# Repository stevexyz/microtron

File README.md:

This is a fork of gigatron that is trying to minimize even more the number of components required.

Original project by Marcel van Kervinck and Walter Belgers can be found at https://gigatron.io

Discussion about microtron can be found at https://forum.gigatron.io/viewtopic.php?t=255

Schematic files are edited with KiCAD 6.

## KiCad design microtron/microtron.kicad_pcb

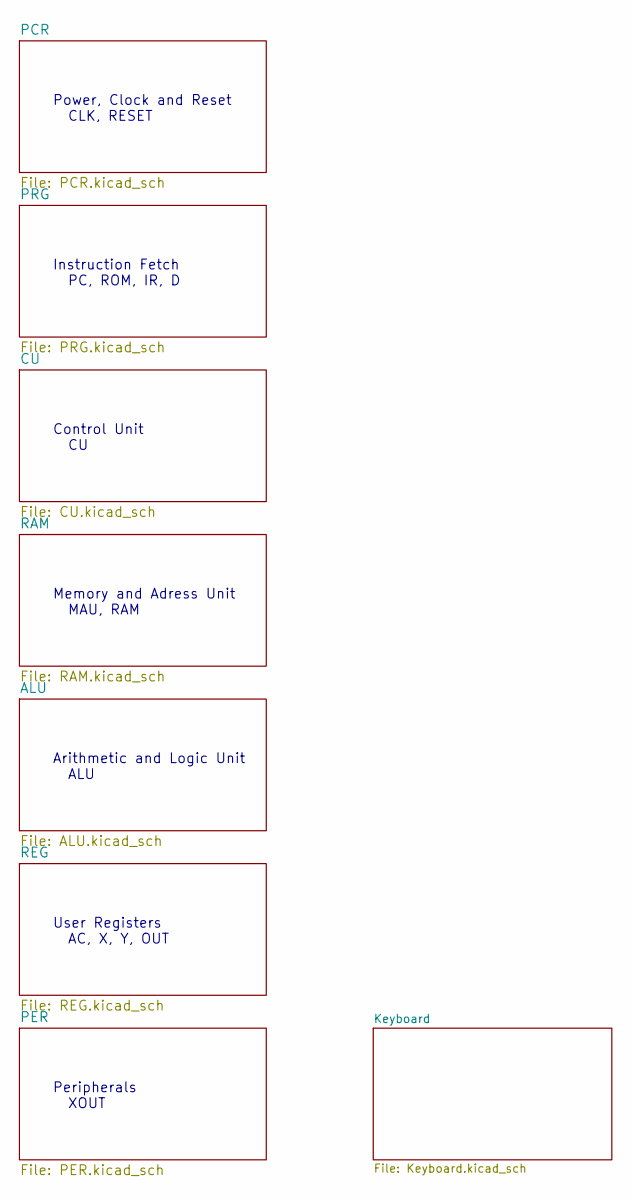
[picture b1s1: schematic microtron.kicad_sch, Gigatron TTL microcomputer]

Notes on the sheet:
Control Unit CU
Instruction Fetch PC, ROM, IR, D
Arithmetic and Logic Unit ALU
Memory and Adress Unit MAU, RAM
User Registers AC, X, Y, OUT
Peripherals XOUT
Power, Clock and Reset CLK, RESET

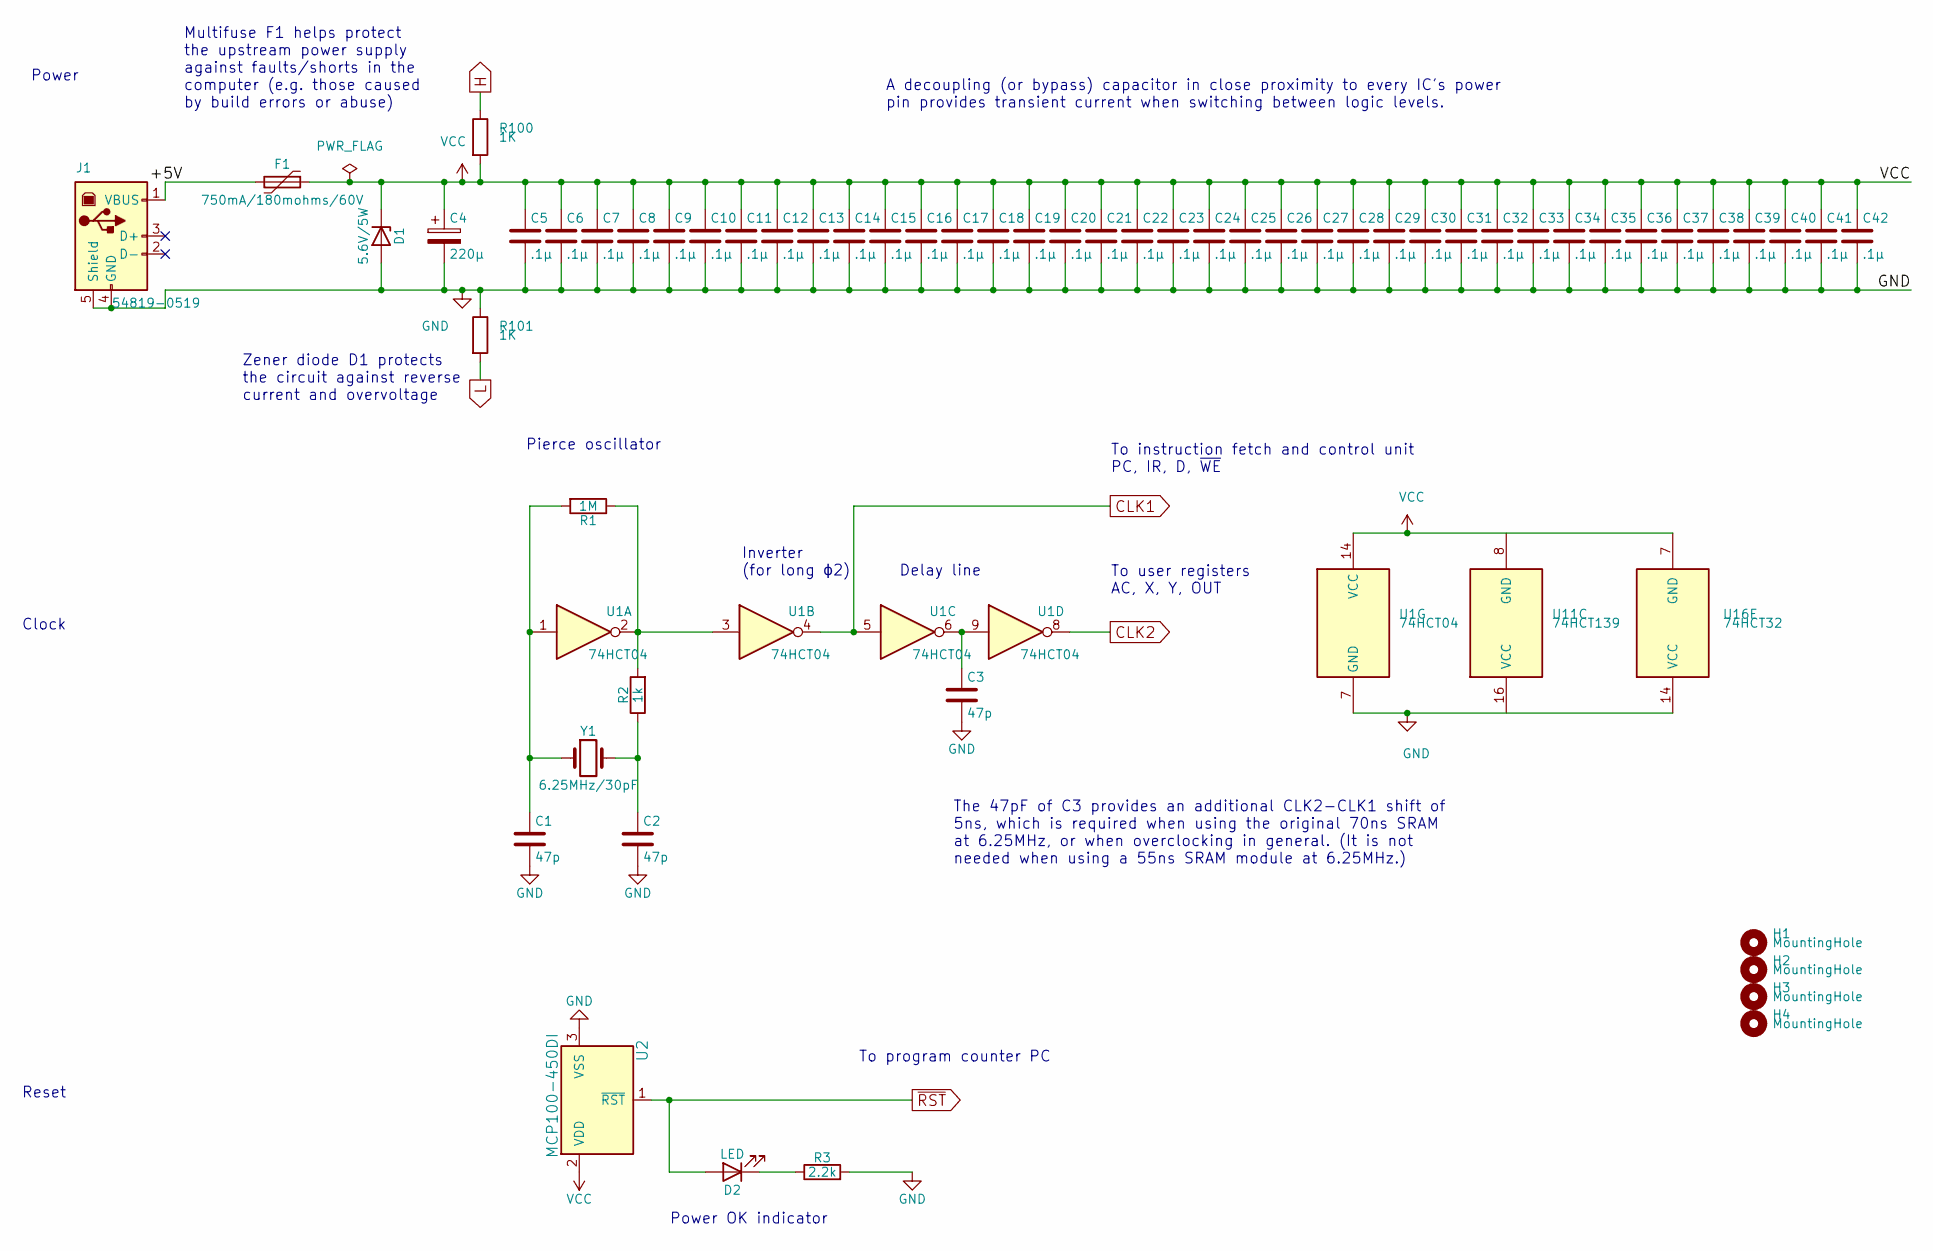
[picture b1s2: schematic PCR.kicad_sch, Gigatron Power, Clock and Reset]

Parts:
C1, C2, C3: 47p; C_Disc_D3.0mm_W2.0mm_P2.50mm
C4: 220µ; CP_Radial_D8.0mm_P3.50mm
C5, C6, C7, C8, C9, C10, C11, C12, C13, C14, C15, C16, C17, C18, C19, C20, C21, C22, C23, C24, C25, C26, C27, C28, C29, C30, C31, C32, C33, C34, C35, C36, C37, C38, C39, C40, C41, C42: .1µ; C_Disc_D4.3mm_W1.9mm_P5.00mm
D1: 5.6V/5W; D_DO-15_P12.70mm_Horizontal
D2: LED; LED_D3.0mm
F1: 750mA/180mohms/60V; Fuse_Littelfuse_395Series
H1, H2, H3, H4: MountingHole; MountingHole_2.7mm_M2.5
J1: 54819-0519; USB_Micro-B_Wuerth_629105150521
R1: 1M; R_Axial_DIN0207_L6.3mm_D2.5mm_P10.16mm_Horizontal
R2: 1k; R_Axial_DIN0207_L6.3mm_D2.5mm_P10.16mm_Horizontal
R3: 2.2k; R_Axial_DIN0207_L6.3mm_D2.5mm_P10.16mm_Horizontal
R100, R101: 1K; R_Axial_DIN0204_L3.6mm_D1.6mm_P1.90mm_Vertical
U1: 74HCT04; DIP-14_W7.62mm
U2: MCP100-450DI; TO-92L_Inline_Wide
U11: 74HCT139; DIP-16_W7.62mm
U16: 74HCT32; DIP-14_W7.62mm
Y1: 6.25MHz/30pF; Crystal_HC49-U_Vertical

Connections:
/PCR/+5V: F1.2, J1.1 (VBUS)
CLK1: U1.4, U1.5; also elsewhere on the board
CLK2: U1.8; also elsewhere on the board
GND: C1.2, C2.2, C3.2, C4.2, C5.2, C6.2, C7.2, C8.2, C9.2, C10.2, C11.2, C12.2, C13.2, C14.2, C15.2, C16.2, C17.2, C18.2, C19.2, C20.2, C21.2, C22.2, C23.2, C24.2, C25.2, C26.2, C27.2, C28.2, C29.2, C30.2, C31.2, C32.2, C33.2, C34.2, C35.2, C36.2, C37.2, C38.2, C39.2, C40.2, C41.2, C42.2, D1.2 (A), J1.4 (GND), J1.5 (Shield), R3.2, R101.1, U1.7 (GND), U2.3 (VSS), U16.14 (VCC); also elsewhere on the board
H: R100.1; also elsewhere on the board
L: R101.2; also elsewhere on the board
unnamed: C1.1, R1.2, U1.1, Y1.1
unnamed: C2.1, R2.1, Y1.2
unnamed: C3.1, U1.6, U1.9
unnamed: D2.1 (K), R3.1
unnamed: R1.1, R2.2, U1.2
VCC: C4.1, C5.1, C6.1, C7.1, C8.1, C9.1, C10.1, C11.1, C12.1, C13.1, C14.1, C15.1, C16.1, C17.1, C18.1, C19.1, C20.1, C21.1, C22.1, C23.1, C24.1, C25.1, C26.1, C27.1, C28.1, C29.1, C30.1, C31.1, C32.1, C33.1, C34.1, C35.1, C36.1, C37.1, C38.1, C39.1, C40.1, C41.1, C42.1, D1.1 (K), F1.1, R100.2, U1.14 (VCC), U2.2 (VDD), U16.7 (GND); also elsewhere on the board
~RST: D2.2 (A), U2.1 (~RST); also elsewhere on the board

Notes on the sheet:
To user registers AC, X, Y, OUT
Zener diode D1 protects the circuit against reverse current and overvoltage
Clock
The 47pF of C3 provides an additional CLK2-CLK1 shift of 5ns, which is required when using the original 70ns SRAM at 6.25MHz, or when overclocking in general. (It is not needed when using a 55ns SRAM module at 6.25MHz.)
Multifuse F1 helps protect the upstream power supply against faults/shorts in the computer (e.g. those caused by build errors or abuse)
To instruction fetch and control unit PC, IR, D, ~{WE}
A decoupling (or bypass) capacitor in close proximity to every IC's power pin provides transient current when switching between logic levels.
Power OK indicator
Power
Inverter (for long ɸ2)
Pierce oscillator
Reset
Delay line
To program counter PC

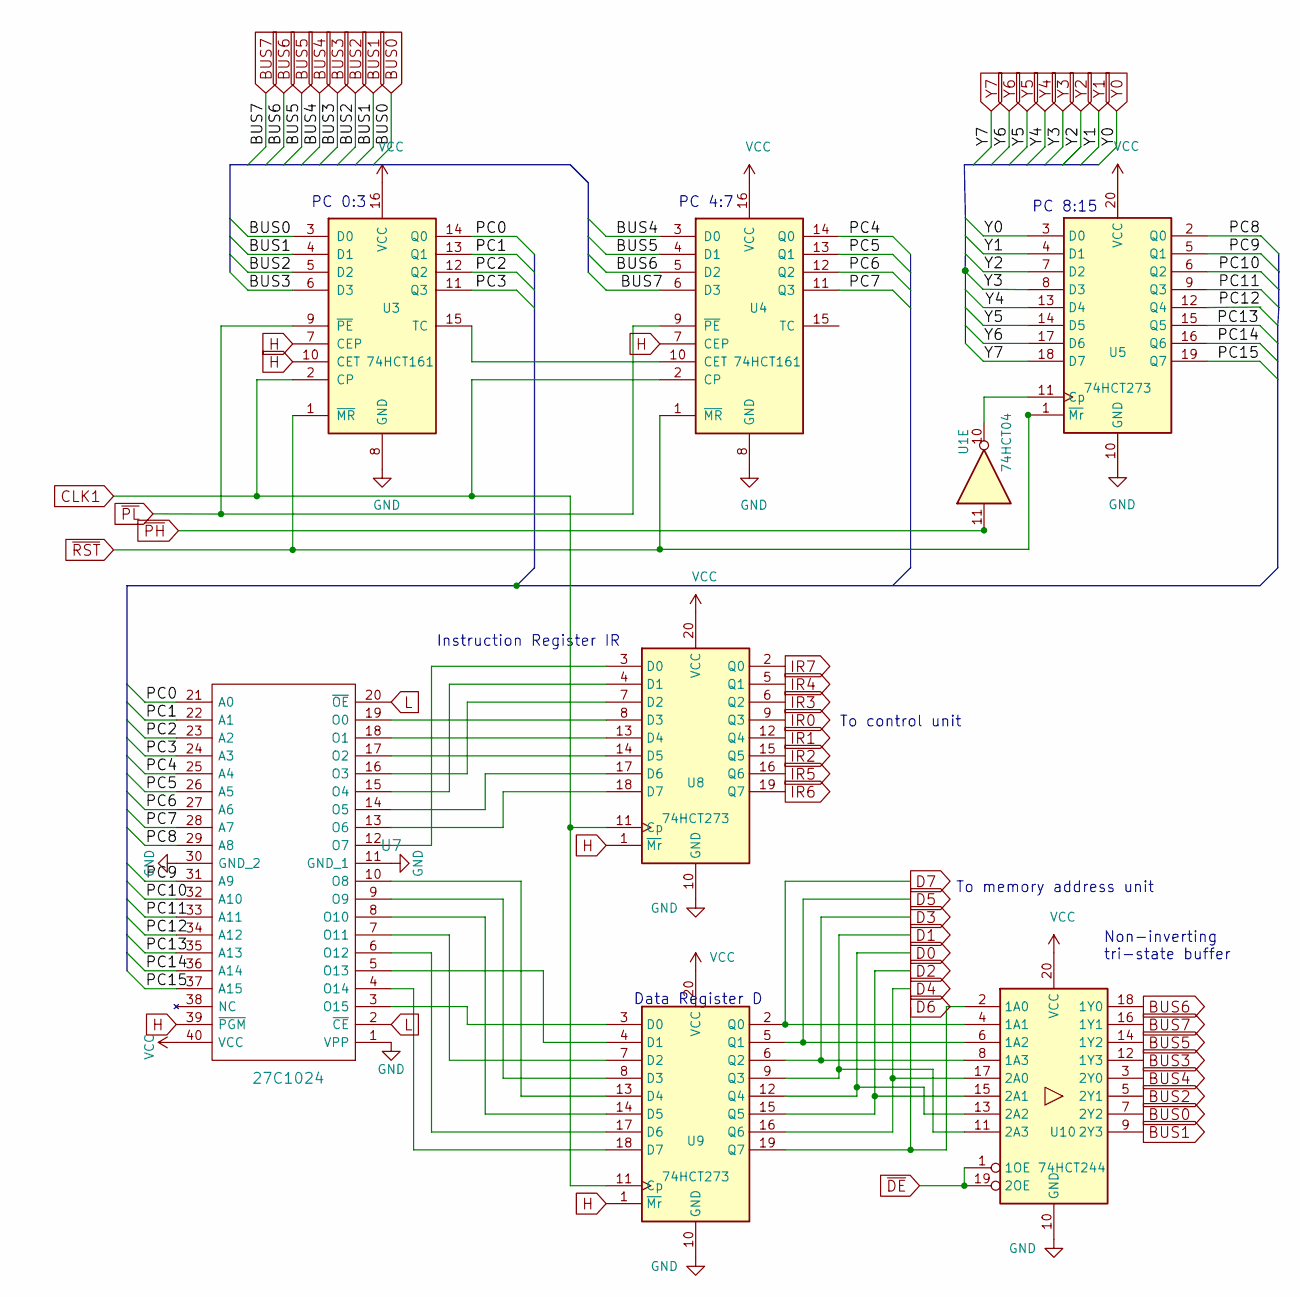
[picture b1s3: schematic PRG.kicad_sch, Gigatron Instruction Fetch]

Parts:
U1: 74HCT04; DIP-14_W7.62mm
U3, U4: 74HCT161; DIP-16_W7.62mm
U5, U8, U9: 74HCT273; DIP-20_W7.62mm
U7: 27C1024; DIP-40_W15.24mm
U10: 74HCT244; DIP-20_W7.62mm

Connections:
/PRG/PC0: U3.14 (Q0), U7.21 (A0)
/PRG/PC1: U3.13 (Q1), U7.22 (A1)
/PRG/PC2: U3.12 (Q2), U7.23 (A2)
/PRG/PC3: U3.11 (Q3), U7.24 (A3)
/PRG/PC4: U4.14 (Q0), U7.25 (A4)
/PRG/PC5: U4.13 (Q1), U7.26 (A5)
/PRG/PC6: U4.12 (Q2), U7.27 (A6)
/PRG/PC7: U4.11 (Q3), U7.28 (A7)
/PRG/PC8: U5.2 (Q0), U7.29 (A8)
/PRG/PC9: U5.5 (Q1), U7.31 (A9)
/PRG/PC10: U5.6 (Q2), U7.32 (A10)
/PRG/PC11: U5.9 (Q3), U7.33 (A11)
/PRG/PC12: U5.12 (Q4), U7.34 (A12)
/PRG/PC13: U5.15 (Q5), U7.35 (A13)
/PRG/PC14: U5.16 (Q6), U7.36 (A14)
/PRG/PC15: U5.19 (Q7), U7.37 (A15)
BUS0: U3.3 (D0), U10.7 (2Y2); also elsewhere on the board
BUS1: U3.4 (D1), U10.9 (2Y3); also elsewhere on the board
BUS2: U3.5 (D2), U10.5 (2Y1); also elsewhere on the board
BUS3: U3.6 (D3), U10.12 (1Y3); also elsewhere on the board
BUS4: U4.3 (D0), U10.3 (2Y0); also elsewhere on the board
BUS5: U4.4 (D1), U10.14 (1Y2); also elsewhere on the board
BUS6: U4.5 (D2), U10.18 (1Y0); also elsewhere on the board
BUS7: U4.6 (D3), U10.16 (1Y1); also elsewhere on the board
CLK1: U3.2 (CP), U4.2 (CP), U8.11 (Cp), U9.11 (Cp); also elsewhere on the board
D0: U9.12 (Q4), U10.13 (2A2); also elsewhere on the board
D1: U9.9 (Q3), U10.11 (2A3); also elsewhere on the board
D2: U9.15 (Q5), U10.15 (2A1); also elsewhere on the board
D3: U9.6 (Q2), U10.8 (1A3); also elsewhere on the board
D4: U9.16 (Q6), U10.17 (2A0); also elsewhere on the board
D5: U9.5 (Q1), U10.6 (1A2); also elsewhere on the board
D6: U9.19 (Q7), U10.2 (1A0); also elsewhere on the board
D7: U9.2 (Q0), U10.4 (1A1); also elsewhere on the board
GND: U3.8 (GND), U4.8 (GND), U5.10 (GND), U7.1 (VPP), U7.11 (GND_1), U7.30 (GND_2), U8.10 (GND), U9.10 (GND), U10.10 (GND); also elsewhere on the board
H: U3.7 (CEP), U3.10 (CET), U4.7 (CEP), U7.39 (~PGM), U8.1 (~Mr), U9.1 (~Mr); also elsewhere on the board
IR0: U8.9 (Q3); also elsewhere on the board
IR1: U8.12 (Q4); also elsewhere on the board
IR2: U8.15 (Q5); also elsewhere on the board
IR3: U8.6 (Q2); also elsewhere on the board
IR4: U8.5 (Q1); also elsewhere on the board
IR5: U8.16 (Q6); also elsewhere on the board
IR6: U8.19 (Q7); also elsewhere on the board
IR7: U8.2 (Q0); also elsewhere on the board
L: U7.2 (~CE), U7.20 (~OE); also elsewhere on the board
unnamed: U1.10, U5.11 (Cp)
unnamed: U3.15 (TC), U4.10 (CET)
unnamed: U7.3 (O15), U9.3 (D0)
unnamed: U7.4 (O14), U9.18 (D7)
unnamed: U7.5 (O13), U9.4 (D1)
unnamed: U7.6 (O12), U9.17 (D6)
unnamed: U7.7 (O11), U9.7 (D2)
unnamed: U7.8 (O10), U9.14 (D5)
unnamed: U7.9 (O9), U9.8 (D3)
unnamed: U7.10 (O8), U9.13 (D4)
unnamed: U7.12 (O7), U8.3 (D0)
unnamed: U7.13 (O6), U8.18 (D7)
unnamed: U7.14 (O5), U8.17 (D6)
unnamed: U7.15 (O4), U8.4 (D1)
unnamed: U7.16 (O3), U8.7 (D2)
unnamed: U7.17 (O2), U8.14 (D5)
unnamed: U7.18 (O1), U8.13 (D4)
unnamed: U7.19 (O0), U8.8 (D3)
VCC: U3.16 (VCC), U4.16 (VCC), U5.20 (VCC), U7.40 (VCC), U8.20 (VCC), U9.20 (VCC), U10.20 (VCC); also elsewhere on the board
Y0: U5.3 (D0); also elsewhere on the board
Y1: U5.4 (D1); also elsewhere on the board
Y2: U5.7 (D2); also elsewhere on the board
Y3: U5.8 (D3); also elsewhere on the board
Y4: U5.13 (D4); also elsewhere on the board
Y5: U5.14 (D5); also elsewhere on the board
Y6: U5.17 (D6); also elsewhere on the board
Y7: U5.18 (D7); also elsewhere on the board
~DE: U10.1 (1OE), U10.19 (2OE); also elsewhere on the board
~PL: U3.9 (~PE), U4.9 (~PE); also elsewhere on the board
~RST: U3.1 (~MR), U4.1 (~MR), U5.1 (~Mr); also elsewhere on the board

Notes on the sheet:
Data Register D
PC 0:3
To control unit
Non-inverting tri-state buffer
Instruction Register IR
PC 8:15
PC 4:7
To memory address unit

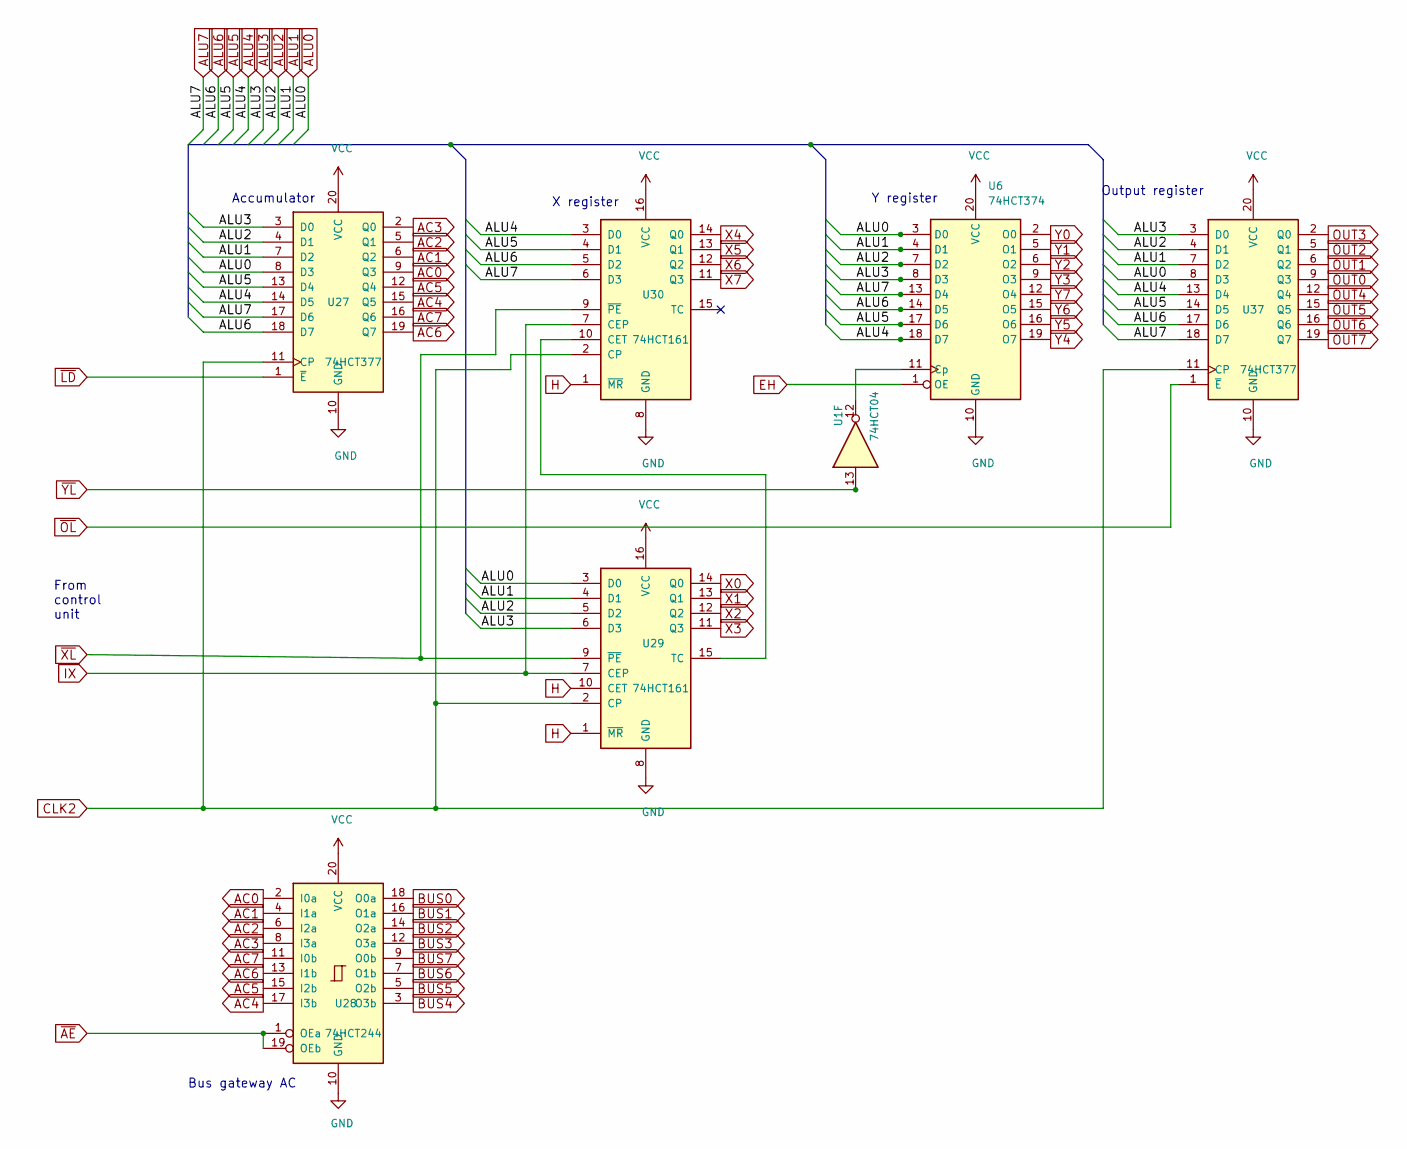
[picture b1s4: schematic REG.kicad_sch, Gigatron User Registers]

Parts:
U1: 74HCT04; DIP-14_W7.62mm
U6: 74HCT374; DIP-20_W7.62mm
U27, U37: 74HCT377; DIP-20_W7.62mm
U28: 74HCT244; DIP-20_W7.62mm
U29, U30: 74HCT161; DIP-16_W7.62mm

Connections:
AC0: U27.9 (Q3), U28.2 (I0a); also elsewhere on the board
AC1: U27.6 (Q2), U28.4 (I1a); also elsewhere on the board
AC2: U27.5 (Q1), U28.6 (I2a); also elsewhere on the board
AC3: U27.2 (Q0), U28.8 (I3a); also elsewhere on the board
AC4: U27.15 (Q5), U28.17 (I3b); also elsewhere on the board
AC5: U27.12 (Q4), U28.15 (I2b); also elsewhere on the board
AC6: U27.19 (Q7), U28.13 (I1b); also elsewhere on the board
AC7: U27.16 (Q6), U28.11 (I0b); also elsewhere on the board
ALU0: U27.8 (D3), U29.3 (D0), U37.8 (D3); also elsewhere on the board
ALU1: U27.7 (D2), U29.4 (D1), U37.7 (D2); also elsewhere on the board
ALU2: U27.4 (D1), U29.5 (D2), U37.4 (D1); also elsewhere on the board
ALU3: U27.3 (D0), U29.6 (D3), U37.3 (D0); also elsewhere on the board
ALU4: U27.14 (D5), U30.3 (D0), U37.13 (D4); also elsewhere on the board
ALU5: U27.13 (D4), U30.4 (D1), U37.14 (D5); also elsewhere on the board
ALU6: U27.18 (D7), U30.5 (D2), U37.17 (D6); also elsewhere on the board
ALU7: U27.17 (D6), U30.6 (D3), U37.18 (D7); also elsewhere on the board
BUS0: U28.18 (O0a); also elsewhere on the board
BUS1: U28.16 (O1a); also elsewhere on the board
BUS2: U28.14 (O2a); also elsewhere on the board
BUS3: U28.12 (O3a); also elsewhere on the board
BUS4: U28.3 (O3b); also elsewhere on the board
BUS5: U28.5 (O2b); also elsewhere on the board
BUS6: U28.7 (O1b); also elsewhere on the board
BUS7: U28.9 (O0b); also elsewhere on the board
CLK2: U27.11 (CP), U29.2 (CP), U30.2 (CP), U37.11 (CP); also elsewhere on the board
EH: U6.1 (OE); also elsewhere on the board
GND: U6.10 (GND), U27.10 (GND), U28.10 (GND), U29.8 (GND), U30.8 (GND), U37.10 (GND); also elsewhere on the board
H: U29.1 (~MR), U29.10 (CET), U30.1 (~MR); also elsewhere on the board
IX: U29.7 (CEP), U30.7 (CEP); also elsewhere on the board
unnamed: U1.12, U6.11 (Cp)
unnamed: U29.15 (TC), U30.10 (CET)
OUT0: U37.9 (Q3); also elsewhere on the board
OUT1: U37.6 (Q2); also elsewhere on the board
OUT2: U37.5 (Q1); also elsewhere on the board
OUT3: U37.2 (Q0); also elsewhere on the board
OUT4: U37.12 (Q4); also elsewhere on the board
OUT5: U37.15 (Q5); also elsewhere on the board
OUT6: U37.16 (Q6); also elsewhere on the board
OUT7: U37.19 (Q7); also elsewhere on the board
VCC: U6.20 (VCC), U27.20 (VCC), U28.20 (VCC), U29.16 (VCC), U30.16 (VCC), U37.20 (VCC); also elsewhere on the board
X0: U29.14 (Q0); also elsewhere on the board
X1: U29.13 (Q1); also elsewhere on the board
X2: U29.12 (Q2); also elsewhere on the board
X3: U29.11 (Q3); also elsewhere on the board
X4: U30.14 (Q0); also elsewhere on the board
X5: U30.13 (Q1); also elsewhere on the board
X6: U30.12 (Q2); also elsewhere on the board
X7: U30.11 (Q3); also elsewhere on the board
Y0: U6.2 (O0); also elsewhere on the board
Y1: U6.5 (O1); also elsewhere on the board
Y2: U6.6 (O2); also elsewhere on the board
Y3: U6.9 (O3); also elsewhere on the board
Y4: U6.19 (O7); also elsewhere on the board
Y5: U6.16 (O6); also elsewhere on the board
Y6: U6.15 (O5); also elsewhere on the board
Y7: U6.12 (O4); also elsewhere on the board
~AE: U28.1 (OEa), U28.19 (OEb); also elsewhere on the board
~LD: U27.1 (~E); also elsewhere on the board
~OL: U37.1 (~E); also elsewhere on the board
~XL: U29.9 (~PE), U30.9 (~PE); also elsewhere on the board

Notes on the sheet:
Accumulator
Output register
Bus gateway AC
X register
Y register
From control unit

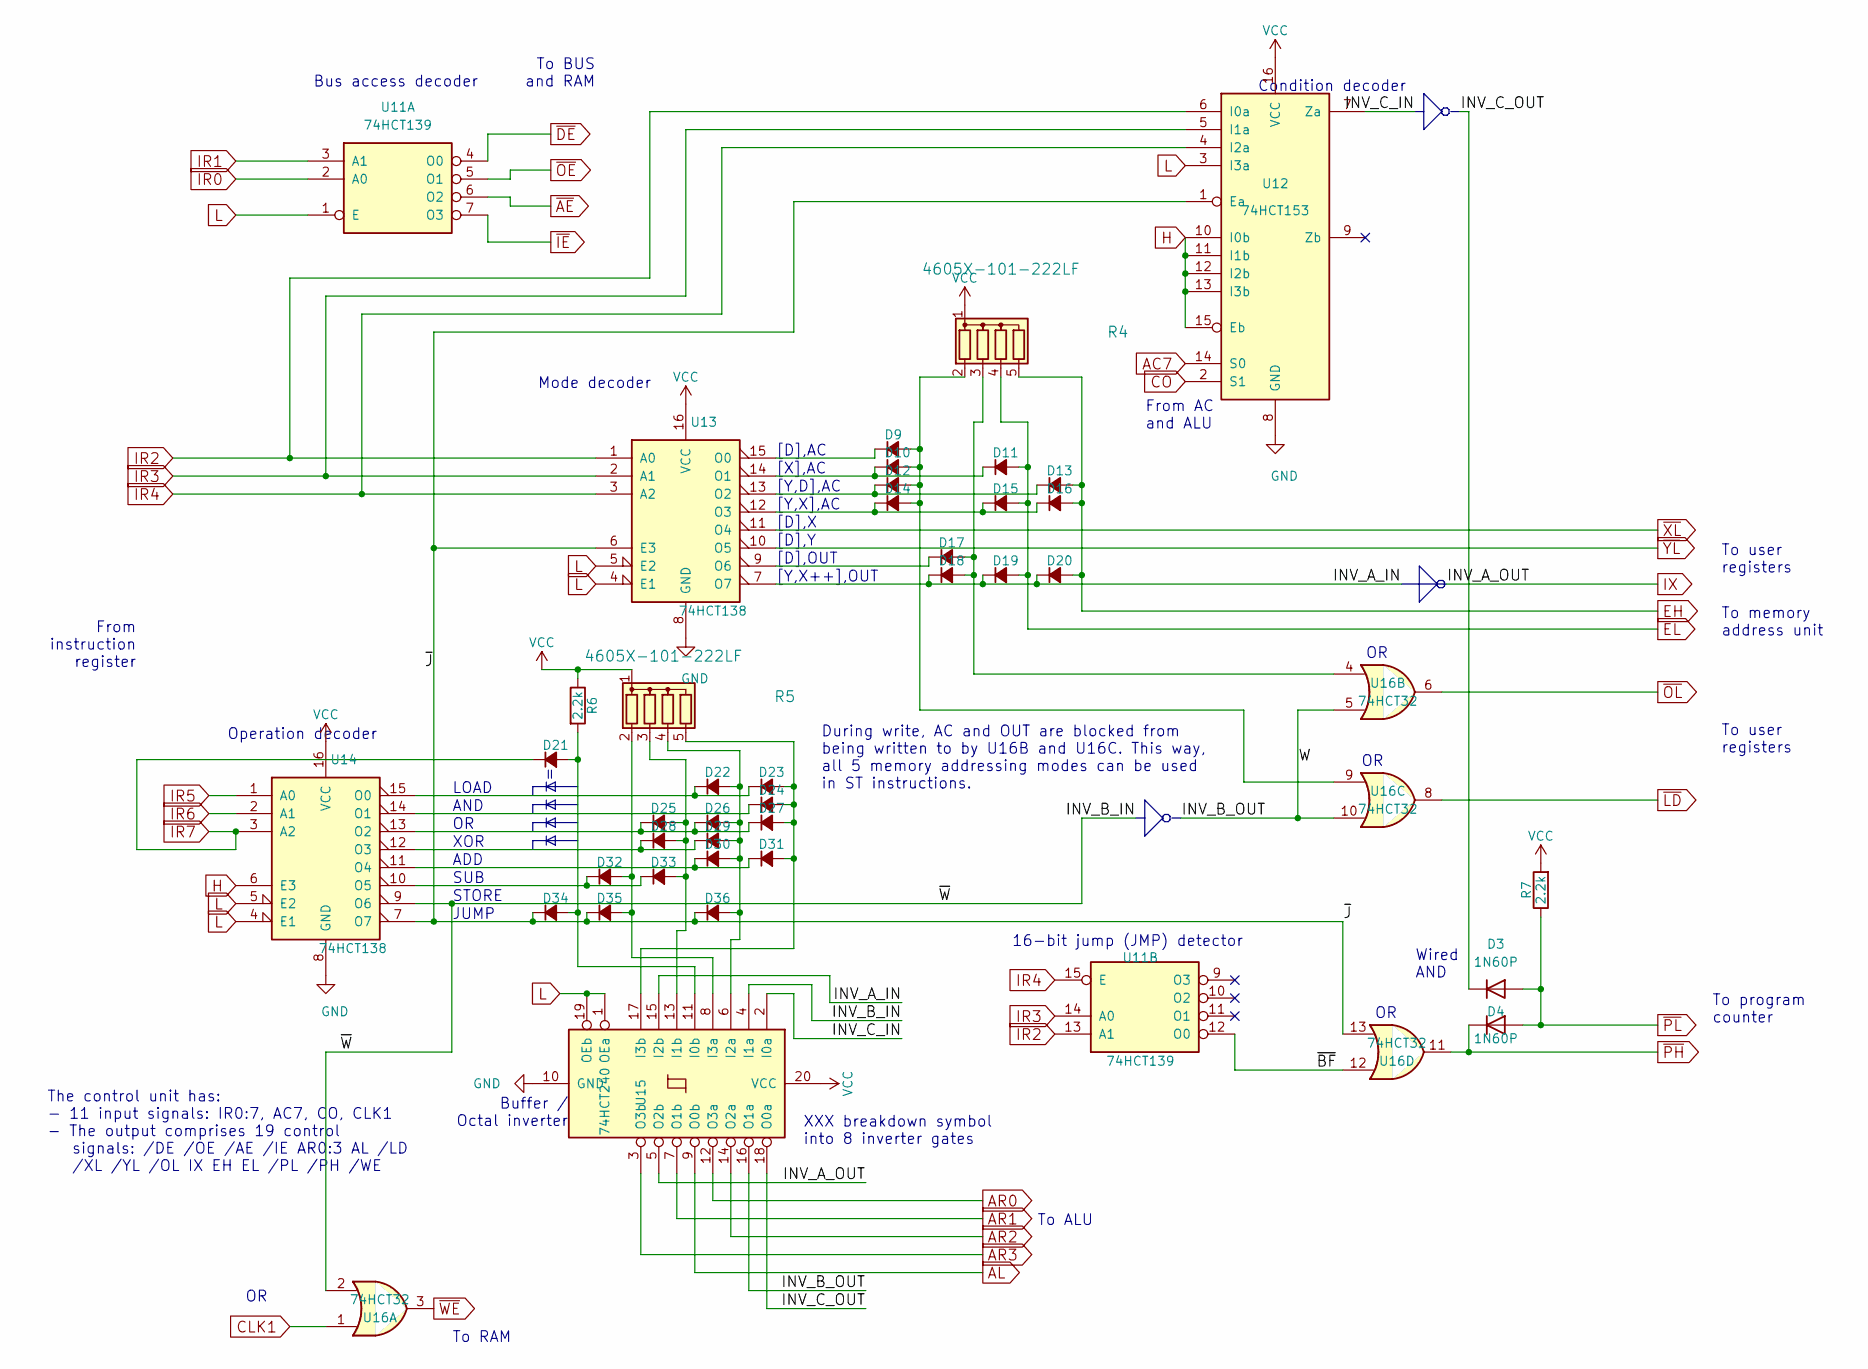
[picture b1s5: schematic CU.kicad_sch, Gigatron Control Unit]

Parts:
D3, D4: 1N60P; D_A-405_P7.62mm_Horizontal
D9, D10, D11, D12, D13, D14, D15, D16, D17, D18, D19, D20, D21, D22, D23, D24, D25, D26, D27, D28, D29, D30, D31, D32, D33, D34, D35, D36: 1N60P; D_A-405_P2.54mm_Vertical_KathodeUp
R4, R5: 4605X-101-222LF; R_Array_SIP5
R6, R7: 2.2k; R_Axial_DIN0207_L6.3mm_D2.5mm_P10.16mm_Horizontal
U11: 74HCT139; DIP-16_W7.62mm
U12: 74HCT153; DIP-16_W7.62mm
U13, U14: 74HCT138; DIP-16_W7.62mm
U15: 74HCT240; DIP-20_W7.62mm
U16: 74HCT32; DIP-14_W7.62mm

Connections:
/CU/INV_A_IN: D18.1 (K), D19.1 (K), D20.1 (K), U13.7 (O7), U15.15 (I2b)
/CU/INV_B_IN: U14.9 (O6), U15.4 (I1a), U16.2
/CU/INV_B_OUT: U15.16 (O1a), U16.5, U16.10
/CU/INV_C_IN: U12.7 (Za), U15.2 (I0a)
/CU/INV_C_OUT: D3.1 (K), U15.18 (O0a)
/CU/~BF: U11.12 (O0), U16.12
/CU/~J: D34.1 (K), D35.1 (K), D36.1 (K), U12.1 (Ea), U13.6 (E3), U14.7 (O7), U16.13
AC7: U12.14 (S0); also elsewhere on the board
AL: U15.9 (O0b); also elsewhere on the board
AR0: U15.12 (O3a); also elsewhere on the board
AR1: U15.7 (O1b); also elsewhere on the board
AR2: U15.14 (O2a); also elsewhere on the board
AR3: U15.3 (O3b); also elsewhere on the board
CLK1: U16.1; also elsewhere on the board
CO: U12.2 (S1); also elsewhere on the board
EH: D13.2 (A), D16.2 (A), D20.2 (A), R4.5 (R4); also elsewhere on the board
EL: D11.2 (A), D15.2 (A), D19.2 (A), R4.4 (R3); also elsewhere on the board
GND: U12.8 (GND), U13.8 (GND), U14.8 (GND), U15.10 (GND); also elsewhere on the board
H: U12.10 (I0b), U12.11 (I1b), U12.12 (I2b), U12.13 (I3b), U12.15 (Eb), U14.6 (E3); also elsewhere on the board
IR0: U11.2 (A0); also elsewhere on the board
IR1: U11.3 (A1); also elsewhere on the board
IR2: U11.13 (A1), U12.6 (I0a), U13.1 (A0); also elsewhere on the board
IR3: U11.14 (A0), U12.5 (I1a), U13.2 (A1); also elsewhere on the board
IR4: U11.15 (E), U12.4 (I2a), U13.3 (A2); also elsewhere on the board
IR5: U14.1 (A0); also elsewhere on the board
IR6: U14.2 (A1); also elsewhere on the board
IR7: D21.1 (K), U14.3 (A2); also elsewhere on the board
IX: U15.5 (O2b); also elsewhere on the board
L: U11.1 (E), U12.3 (I3a), U13.4 (E1), U13.5 (E2), U14.4 (E1), U14.5 (E2), U15.1 (OEa), U15.19 (OEb); also elsewhere on the board
unnamed: D9.1 (K), U13.15 (O0)
unnamed: D10.1 (K), D11.1 (K), U13.14 (O1)
unnamed: D9.2 (A), D10.2 (A), D12.2 (A), D14.2 (A), R4.2 (R1), U16.9
unnamed: D12.1 (K), D13.1 (K), U13.13 (O2)
unnamed: D14.1 (K), D15.1 (K), D16.1 (K), U13.12 (O3)
unnamed: D17.1 (K), U13.9 (O6)
unnamed: D17.2 (A), D18.2 (A), R4.3 (R2), U16.4
unnamed: D21.2 (A), D34.2 (A), R6.2, U15.11 (I0b)
unnamed: D22.1 (K), D23.1 (K), U14.15 (O0)
unnamed: D22.2 (A), D26.2 (A), D29.2 (A), D30.2 (A), D36.2 (A), R5.4 (R3), U15.6 (I2a)
unnamed: D23.2 (A), D24.2 (A), D27.2 (A), D31.2 (A), R5.5 (R4), U15.17 (I3b)
unnamed: D24.1 (K), U14.14 (O1)
unnamed: D25.1 (K), D26.1 (K), D27.1 (K), U14.13 (O2)
unnamed: D25.2 (A), D28.2 (A), D33.2 (A), R5.3 (R2), U15.13 (I1b)
unnamed: D28.1 (K), D29.1 (K), U14.12 (O3)
unnamed: D30.1 (K), D31.1 (K), U14.11 (O4)
unnamed: D32.1 (K), D33.1 (K), U14.10 (O5)
unnamed: D32.2 (A), D35.2 (A), R5.2 (R1), U15.8 (I3a)
VCC: R4.1 (common), R5.1 (common), R6.1, R7.2, U12.16 (VCC), U13.16 (VCC), U14.16 (VCC), U15.20 (VCC); also elsewhere on the board
~AE: U11.6 (O2); also elsewhere on the board
~DE: U11.4 (O0); also elsewhere on the board
~IE: U11.7 (O3); also elsewhere on the board
~LD: U16.8; also elsewhere on the board
~OE: U11.5 (O1); also elsewhere on the board
~OL: U16.6; also elsewhere on the board
~PH: D4.1 (K), U16.11
~PL: D3.2 (A), D4.2 (A), R7.1; also elsewhere on the board
~WE: U16.3; also elsewhere on the board
~XL: U13.11 (O4); also elsewhere on the board
~YL: U13.10 (O5)

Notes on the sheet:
To program counter
JUMP
During write, AC and OUT are blocked from being written to by U16B and U16C. This way, all 5 memory addressing modes can be used in ST instructions.
To user registers
[Y,X],AC
Buffer / Octal inverter
16-bit jump (JMP) detector
From AC and ALU
To RAM
[D],Y
Condition decoder
To memory address unit
Operation decoder
The control unit has: - 11 input signals: IR0:7, AC7, CO, CLK1 - The output comprises 19 control signals: /DE /OE /AE /IE AR0:3 AL /LD /XL /YL /OL IX EH EL /PL /PH /WE
To ALU
XOR
ADD
[D],OUT
STORE
Bus access decoder
[D],X
XXX breakdown symbol into 8 inverter gates
From instruction register
AND
SUB
To BUS and RAM
[Y,D],AC
LOAD
Mode decoder
[D],AC
[Y,X++],OUT
[X],AC
Wired AND

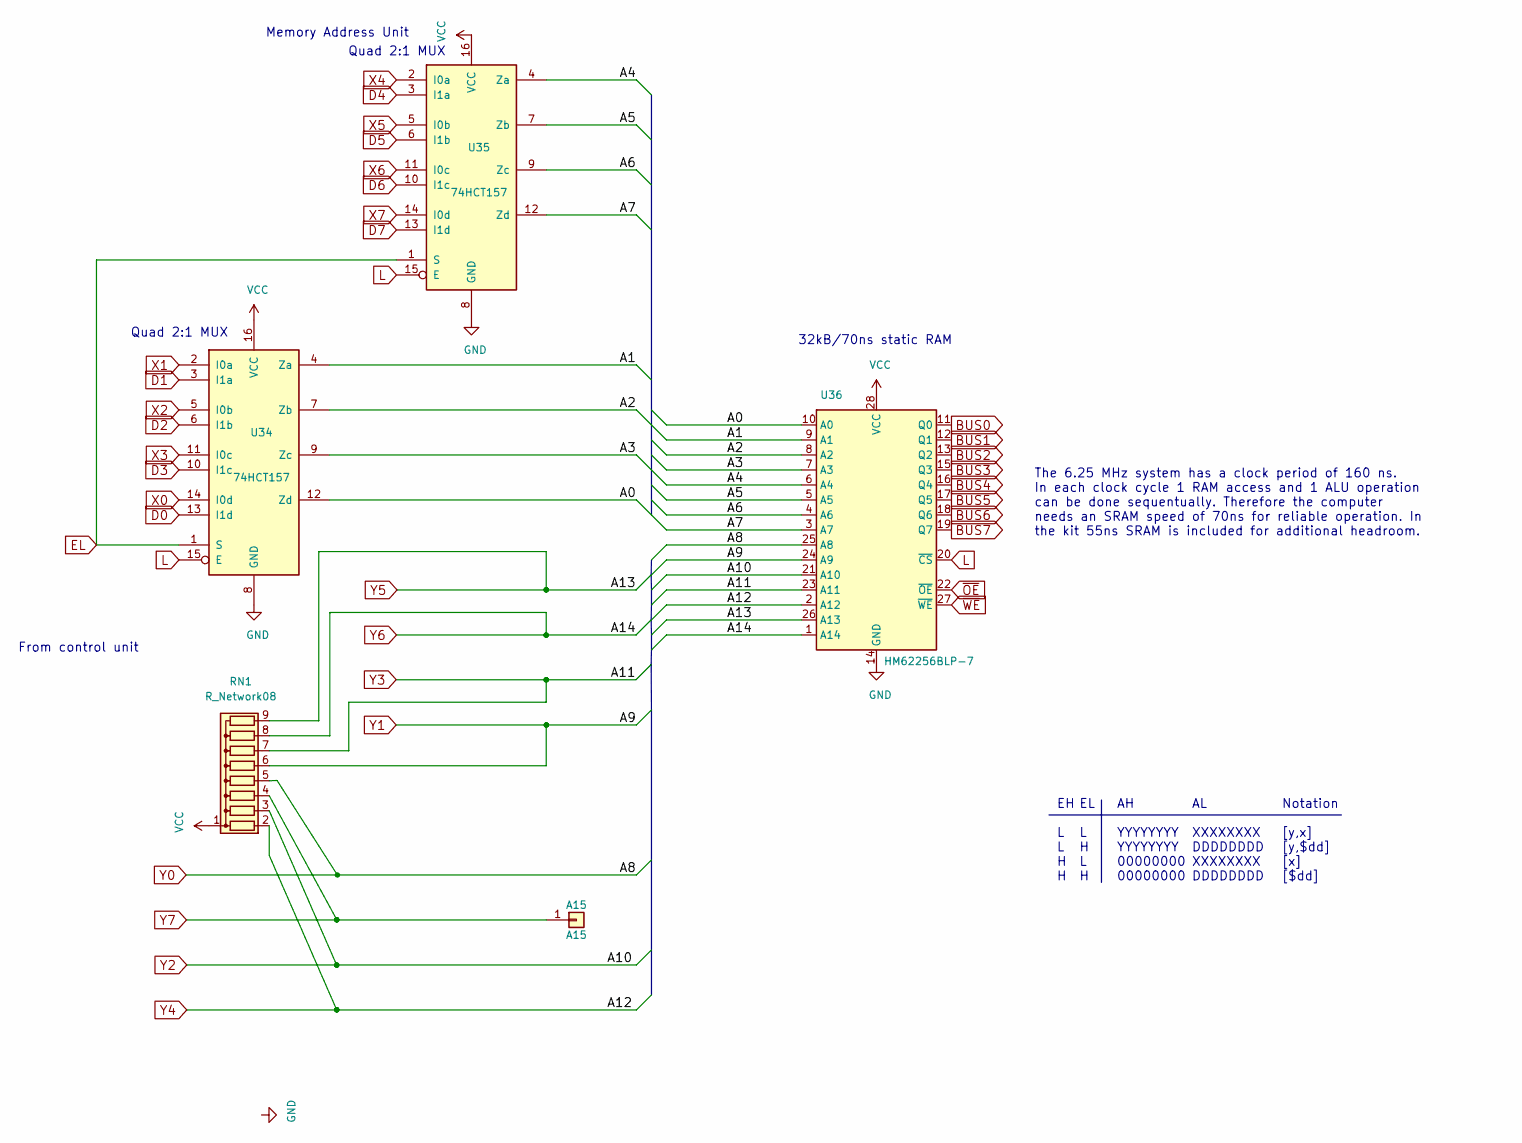
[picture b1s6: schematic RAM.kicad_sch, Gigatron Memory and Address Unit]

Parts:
A15: A15; TestPoint_THTPad_D2.0mm_Drill1.0mm
RN1: R_Network08; R_Array_SIP9
U34, U35: 74HCT157; DIP-16_W7.62mm
U36: HM62256BLP-7; DIP-28_W15.24mm

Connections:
/RAM/A0: U34.12 (Zd), U36.10 (A0)
/RAM/A1: U34.4 (Za), U36.9 (A1)
/RAM/A2: U34.7 (Zb), U36.8 (A2)
/RAM/A3: U34.9 (Zc), U36.7 (A3)
/RAM/A4: U35.4 (Za), U36.6 (A4)
/RAM/A5: U35.7 (Zb), U36.5 (A5)
/RAM/A6: U35.9 (Zc), U36.4 (A6)
/RAM/A7: U35.12 (Zd), U36.3 (A7)
BUS0: U36.11 (Q0); also elsewhere on the board
BUS1: U36.12 (Q1); also elsewhere on the board
BUS2: U36.13 (Q2); also elsewhere on the board
BUS3: U36.15 (Q3); also elsewhere on the board
BUS4: U36.16 (Q4); also elsewhere on the board
BUS5: U36.17 (Q5); also elsewhere on the board
BUS6: U36.18 (Q6); also elsewhere on the board
BUS7: U36.19 (Q7); also elsewhere on the board
D0: U34.13 (I1d); also elsewhere on the board
D1: U34.3 (I1a); also elsewhere on the board
D2: U34.6 (I1b); also elsewhere on the board
D3: U34.10 (I1c); also elsewhere on the board
D4: U35.3 (I1a); also elsewhere on the board
D5: U35.6 (I1b); also elsewhere on the board
D6: U35.10 (I1c); also elsewhere on the board
D7: U35.13 (I1d); also elsewhere on the board
EL: U34.1 (S), U35.1 (S); also elsewhere on the board
GND: U34.8 (GND), U35.8 (GND), U36.14 (GND); also elsewhere on the board
L: U34.15 (E), U35.15 (E), U36.20 (~CS); also elsewhere on the board
VCC: RN1.1 (common), U34.16 (VCC), U35.16 (VCC), U36.28 (VCC); also elsewhere on the board
X0: U34.14 (I0d); also elsewhere on the board
X1: U34.2 (I0a); also elsewhere on the board
X2: U34.5 (I0b); also elsewhere on the board
X3: U34.11 (I0c); also elsewhere on the board
X4: U35.2 (I0a); also elsewhere on the board
X5: U35.5 (I0b); also elsewhere on the board
X6: U35.11 (I0c); also elsewhere on the board
X7: U35.14 (I0d); also elsewhere on the board
Y0: RN1.5 (R4), U36.25 (A8); also elsewhere on the board
Y1: RN1.6 (R5), U36.24 (A9); also elsewhere on the board
Y2: RN1.3 (R2), U36.21 (A10); also elsewhere on the board
Y3: U36.23 (A11); also elsewhere on the board
Y4: RN1.2 (R1), U36.2 (A12); also elsewhere on the board
Y5: RN1.9 (R8), U36.26 (A13); also elsewhere on the board
Y6: RN1.8 (R7), U36.1 (A14); also elsewhere on the board
Y7: A15.1, RN1.4 (R3); also elsewhere on the board
~OE: U36.22 (~OE); also elsewhere on the board
~WE: U36.27 (~WE); also elsewhere on the board

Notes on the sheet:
From control unit
AH YYYYYYYY YYYYYYYY 00000000 00000000
The 6.25 MHz system has a clock period of 160 ns. In each clock cycle 1 RAM access and 1 ALU operation can be done sequentually. Therefore the computer needs an SRAM speed of 70ns for reliable operation. In the kit 55ns SRAM is included for additional headroom.
Quad 2:1 MUX
EH L L H H
AL XXXXXXXX DDDDDDDD XXXXXXXX DDDDDDDD
EL L H L H
32kB/70ns static RAM
Notation [y,x] [y,$dd] [x] [$dd]
Memory Address Unit

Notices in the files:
microtron/microtron.kicad_pcb:
©2017-2020
